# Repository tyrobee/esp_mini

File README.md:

# esp_mini
A Esp  based flight controller which is really tiny and can be controller through almost everything from your phone to anthor esp and cn also be used as swarn drones likw the drones which do all those cool drone lighting show. Actually i made this drone with that idea only ive been seen those swarn drones show in my school and wated to do smtg like that but there not a single affordable platform for that but you can achevie the same results with this drone at a really affordable range.

## compnents 
- Xiao ESP32 S3 (FC)
- MPU 6050
- 8520 Coreless Motor 2xCW & 2xCCW
- 55mm Propeller 2xCW & 2xCCW
- Coustom motor drive:
    • SI2300 1N-MOSFET 4x
    • 1N4148 Diode 4x
    • 10k ohm Resistor 4X
## Frame

# Schematics
 Here is the break down of the connections 
  MOTORS-
  M1 --> A8
  M2 --> A3
  M3 --> A2
  M4 --> A0

  MPU6050-
  SDA --> A4
  SCL --> A5

  CRSF- (you can change this part but as i have a csrf radio i have done it for a csrf receiver)
  RX --> D7
  TX --> D6

  3.7v to 5v-
  for reciver to get powered 

  led-
  2 power led
  1 arm led

  Battery Voltage Telemetry-
  Vin --> A1

# PCB 
The PCB is designed in Kicad 
top -

bottom -

# Firmware

This project uses open-source flight controller firmware from the ESP-FC project,
developed by rtlopez.

- Original firmware repository:
  https://github.com/rtlopez/esp-fc

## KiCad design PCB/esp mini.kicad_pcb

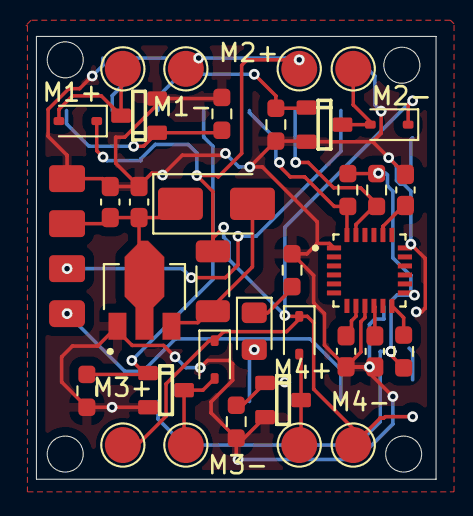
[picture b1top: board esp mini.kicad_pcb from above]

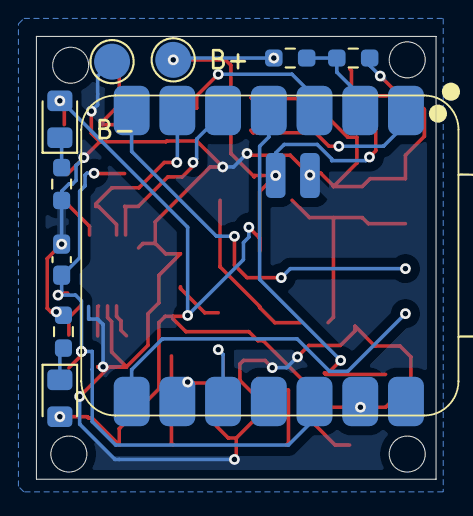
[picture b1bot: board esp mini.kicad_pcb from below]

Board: 2 copper layers, 22.2 x 24.6 mm, 45 parts (10 on the bottom side), 26 nets.

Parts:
B+: B+; TestPoint_Pad_D2.0mm
B-: B-; TestPoint_Pad_D2.0mm
C1, C2, C3, C4: 0.01uF; C_0603_1608Metric_Pad1.08x0.95mm_HandSolder
C5, C6: 12uF; C_0603_1608Metric_Pad1.08x0.95mm_HandSolder
D1, D2, D3, D4: 1N4148WS; D_SOD-323
D5, D6, D7: LED; LED_0805_2012Metric_Pad1.15x1.40mm_HandSolder
D10: SS14; D_SMA
L1: 22uH; L_1206_3216Metric_Pad1.22x1.90mm_HandSolder
M1, M2, M3, M4: SI2300; SOT23_1_
M1+: m1-; TestPoint_Pad_D2.0mm
M1-: m1+; TestPoint_Pad_D2.0mm
M2+: m2+; TestPoint_Pad_D2.0mm
M2-: m2-; TestPoint_Pad_D2.0mm
M3+: m3+; TestPoint_Pad_D2.0mm
M3-: m3-; TestPoint_Pad_D2.0mm
M4+: m4-; TestPoint_Pad_D2.0mm
M4-: m4+; TestPoint_Pad_D2.0mm
PS1: ME2108A33P; CONV_ME2108A33P
R1, R2, R3, R4: 1k; R_0603_1608Metric_Pad0.98x0.95mm_HandSolder
R5, R6, R7, R8, R10: 10k; R_0603_1608Metric_Pad0.98x0.95mm_HandSolder
R9, R11, R12: 150; R_0603_1608Metric_Pad0.98x0.95mm_HandSolder
U3: MPU-6050; QFN50P400X400X95-24N
U10: XIAO-ESP32-S3-SMD; XIAO-ESP32-S3-SMD_PAD
U11: XR2 NANO

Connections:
+3.3V: C4.1, R5.1, R6.1, R7.1, U3.13 (VDD), U10.12 (3V3)
+3.3VA: B+.1, D1.1 (K), D2.1 (K), D3.1 (K), D4.1 (K), D6.2 (A), D7.2 (A), L1.1, M1-.1, M2+.1, M3+.1, M4-.1, R8.1, U10.15 (BAT)
+5V: C5.1, C6.1, D10.1 (K), PS1.2 (VOUT), U11.3 (5V)
/LBAT: D5.2 (A), U10.10 (PA5_A9_D9_MISO)
/M1: M1.1, R1.2, U10.1 (PA02_A0_D0)
/M2: M2.1, R2.2, U10.3 (PA10_A2_D2)
/M3: M3.1, R3.2, U10.4 (PA11_A3_D3)
/M4: M4.1, R4.2, U10.9 (PA7_A8_D8_SCK)
/RX: U10.8 (PB09_A7_D7_RX), U11.1 (RX)
/SCL: R6.2, U3.23 (SCL), U10.6 (PA9_A5_D5_SCL)
/SDA: R7.2, U3.24 (SDA), U10.5 (PA8_A4_D4_SDA)
/TX: U10.7 (PB08_A6_D6_TX), U11.2 (TX)
/VBAT: R8.2, R10.1, U10.2 (PA4_A1_D1)
/int: R5.2, U3.12 (INT)
GND: B-.1, C1.2, C2.2, C3.2, C4.2, C5.2, C6.2, M1.2, M2.2, M3.2, M4.2, PS1.1 (VSS), R1.1, R2.1, R3.1, R4.1, R9.1, R10.2, R11.2, R12.2, U3.1 (CLKIN), U3.9 (AD0), U3.11 (FSYNC), U3.18 (GND), U10.13 (GND), U10.16 (GND), U11.4 (GND)
unnamed: D1.2 (A), M1.3, M1+.1
unnamed: D2.2 (A), M2.3, M2-.1
unnamed: D3.2 (A), M3.3, M3-.1
unnamed: D4.2 (A), M4.3, M4+.1
unnamed: D5.1 (K), R9.2
unnamed: D6.1 (K), R11.1
unnamed: D7.1 (K), R12.1
unnamed: D10.2 (A), L1.2, PS1.3 (LX)
unnamed: C2.1, U3.20 (CPOUT)
unnamed: C3.1, U3.10 (REGOUT)
unnamed: C1.1, U3.8 (VLOGIC)

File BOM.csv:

Item,Description,Quantity,Unit Price($),Total Price($),URL,
XIAO ESP32 S3,Flight Controller ,1,8.82,8.82,https://robocraze.com/products/seeed-studio-xiao-esp32-s3-de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,
8520 Coreless Brushed Motor,Motors ,1 set(4Pcs),6.45,6.45,https://roboticsdna.in/product/coreless-motors-720-series-45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,
55 mm Blade Propeller,Propeller,1set(4Pcs),0.56,0.56,https://roboticsdna.in/product/4pcs-set-55mm-white-propeller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,
1N SI2300 MOSFET,To drive motor ,4,0.046,0.19,https://robu.in/product/si2300-hxy-mosfet-20v-6a-350mw-27mω4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,
1N4148 SMD,Diode,4,0.026,0.10,https://robu.in/product/ac1206fr-0710kl-yageo-res-thick-film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,
10k ohm SMD,Resister,5,0.0052,0.0262,,
1k ohm SMD,Resister,4,0.0030,0.012,,
150 ohm SMD,Resister,3,0.0011,0.0033,,
0.01uF SMD,Capacitor,4,0.0030,0.012,,
LED 0805  SMD,Led,3,0.029,0.097,,
ME2108A33P Module,Boost converter,1,0.57,0.57,https://www.flyrobo.in/1.5v-1.8v-2.5v-3v-3.3v-3.7v-4.2v-5v-d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,
MPU6050,Gyro and accelerometer,1,1.91,1.91,https://robu.in/product/mpu-6050-gyro-sensor-2-accelerometer/,
1S 300mah battery,Battery,1,1.92,1.92,https://robu.in/product/wly702025-300mah-3-7v-single-cell-re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,
RadioMaster XR2 Nano,ELRS recover,1,12.12,12.12,https://rcmumbai.com/products/radiomaster-xr2-nano-2-4ghz-ex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,
PCB,Pcb,5,4.9,4.9,SeedStudio,
Frame,3d printing,1,6.4,0.9,3D,
,,,Shipment,4.56+ 1.66+0.76+0.54+0.65+0.54+1.66 =10.28,,
,,,Tax(3Dprint & Motors ,,2.52,
,,,Total=,51.38 ~ 51.5,,

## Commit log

2026-03-26 Fix spelling and formatting issues in README
    Corrected spelling and formatting in README.
2026-03-26 Fix formatting and spelling in README.md
    Corrected formatting and spelling in the README.
2026-03-26 Update CRSF section with customization note
    Clarified the CRSF section to indicate customization options.
